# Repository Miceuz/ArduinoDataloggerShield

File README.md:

ArduinoDataloggerShield
=======================

SD card datalogger shield for Arduino with two external voltage references. 

I've made this shield because there were no designs in the wild employing external references - this is usefull feature to have when logging analog voltages.

Features: 
 * 74hc125 buffer for level translation
 * 1.20V voltage reference selectable via solder jumper
 * 2.5V voltage reference selectable via solder jumper
 * red indication led
 * green indication led
 * SD card detection
 * SD card write protection detection

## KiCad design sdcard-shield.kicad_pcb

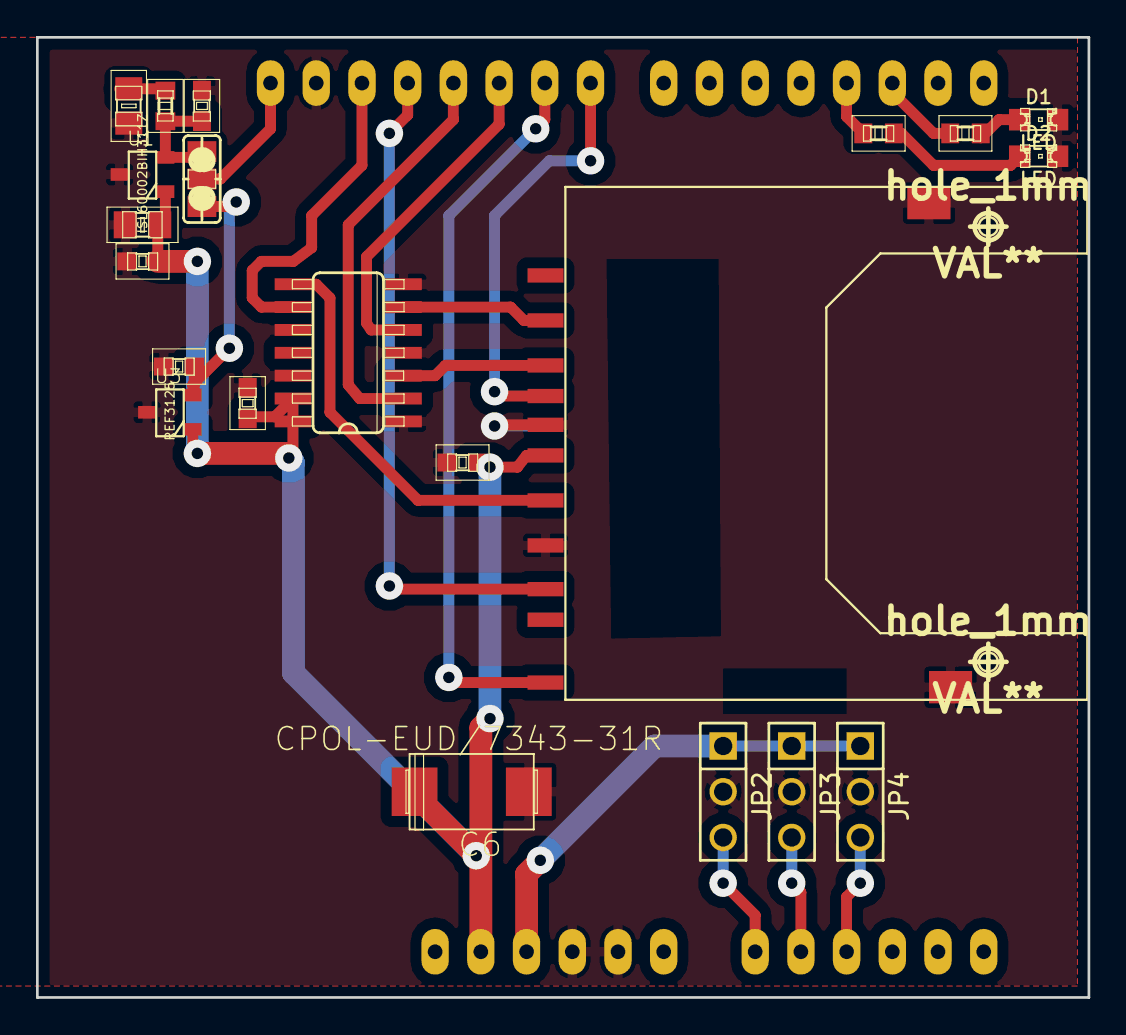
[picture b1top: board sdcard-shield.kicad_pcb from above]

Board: 2 copper layers, 58.4 x 53.3 mm, 24 parts (0 on the bottom side), 23 nets.

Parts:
C1, C4: 10uF; rcl-C0805
C2, C5, C7, C8: 100nF; rcl-C0603
C3: 10nF; rcl-C0603
C6: CPOL-EUD/7343-31R; rcl-D/7343-31R
D1, D2: LED; LED-0805
J1: CON-SD-MMC-1; m-pad-2.1-14-5638-009-511-862
JP1: JUMPER3; jumper-SJ_2
JP2, JP3, JP4: PINHD-1X3; PIN_ARRAY_3X1
R1, R2: 1K; rcl-R0603
R3: 2K; rcl-R0603
SHIELD1: ARDUINO_SHIELD; ARDUINO_SHIELD_2
U1: ISL60002BIH311Z; SOT23
U2: 74LS125; m-pad-2.1-SO14
U3: REF3125; SOT23
hole_1mm, hole_1mm#2: VAL**; hole_1mm

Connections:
+5V: JP2.1, JP3.1, JP4.1, SHIELD1.5V
/2.5V: C8.1, JP1.3, U3.2
/AREF: JP1.2, SHIELD1.AREF
/CARD_DETECT: J1.CD, SHIELD1.8
/CHIP_SELECT: SHIELD1.10, U2.5
/CLK: J1.5, U2.8
/CS: J1.1, U2.6
/DI: J1.2, U2.3
/DO: J1.7, SHIELD1.12
/MOSI: SHIELD1.11, U2.2
/SCK: SHIELD1.13, U2.9
/WRITE_PROTECT: J1.WP, SHIELD1.9
GND: C1.2, C2.2, C3.2, C4.2, C5.2, C6.-, C7.2, C8.2, D1.2, D2.2, J1.3, J1.6, J1.GND, J1.P$1, JP2.2, JP3.2, JP4.2, SHIELD1.GND1, SHIELD1.GND2, SHIELD1.GND3, U1.3, U2.1, U2.4, U2.7, U2.10, U2.12, U3.3
unnamed: C3.1, JP1.1, R3.2, U1.2
unnamed: C4.1, R3.1
unnamed: D2.1, R2.1
unnamed: D1.1, R1.1
unnamed: R2.2, SHIELD1.3
unnamed: R1.2, SHIELD1.2
unnamed: JP4.3, SHIELD1.AD2
unnamed: JP3.3, SHIELD1.AD1
unnamed: JP2.3, SHIELD1.AD0
VCC: C1.1, C2.1, C5.1, C6.+, C7.1, J1.4, SHIELD1.3V3, U1.1, U2.13, U2.14, U3.1

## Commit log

2013-02-14 image
2013-02-27 support 3 adc channels
